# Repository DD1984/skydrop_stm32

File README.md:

this is port of SkyDrop vario to stm32vldiscovery board

origin code:
https://github.com/fhorinek/SkyDrop
website:
http://skybean.eu

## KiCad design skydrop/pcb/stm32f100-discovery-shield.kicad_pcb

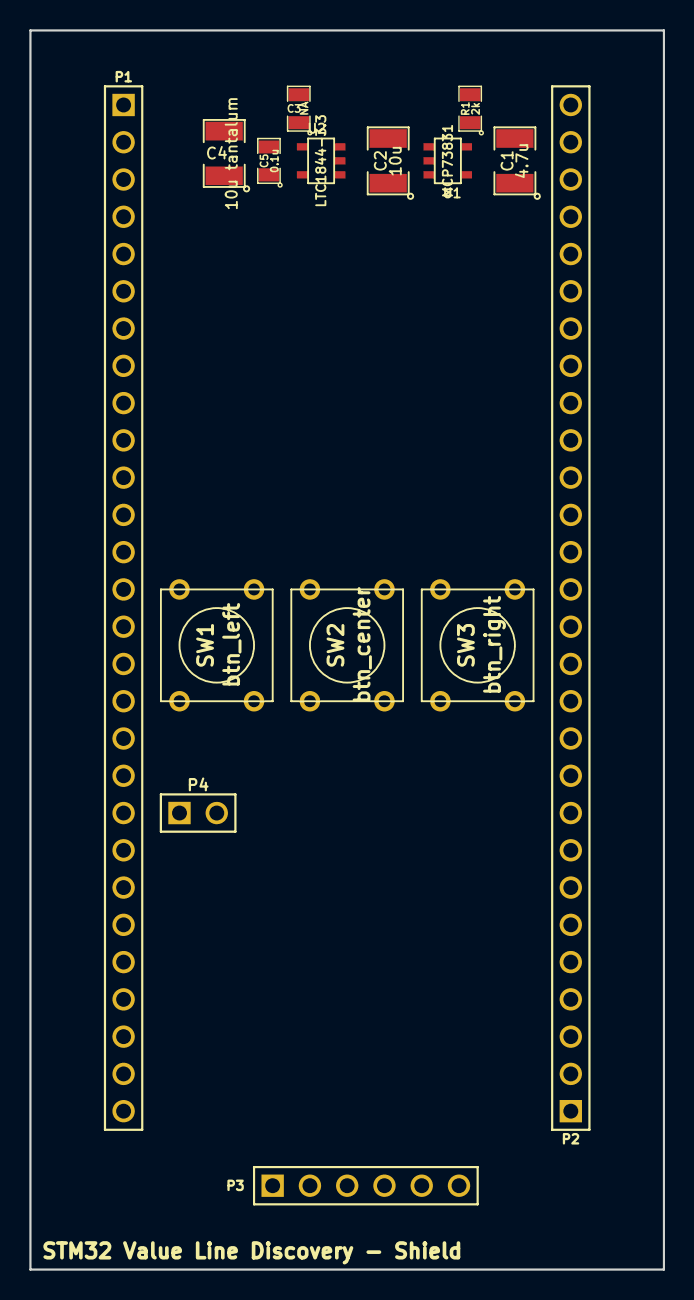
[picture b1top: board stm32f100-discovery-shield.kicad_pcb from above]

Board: 2 copper layers, 43.2 x 84.5 mm, 15 parts (0 on the bottom side), 9 nets, no tracks yet.

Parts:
C1: 4.7u; SM1210
C2: 10u; SM1210
C3: NA; SM0805
C4: 10u tantalum; SM1210
C5: 0.1u; SM0805
P1, P2: CONN28; PIN_ARRAY_28X1
P3: CONN6; PIN_ARRAY_6X1
P4: CONN_2; PIN_ARRAY_2X1
R1: 2k; SM0805
SW1: btn_left; SW_PUSH_SMALL
SW2: btn_center; SW_PUSH_SMALL
SW3: btn_right; SW_PUSH_SMALL
U1: MCP73831; SOT23-5
U2: LTC1844-3.3; SOT23-5

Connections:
+3.3V: C4.1, C5.1, P4.1, SW1.1, SW3.1, U2.5
+5V: C1.1, P2.26, U1.4
+BATT: C2.1, U1.3, U2.1
GND: C1.2, C2.2, C3.2, C4.2, C5.2, P1.1, P1.28, P2.1, P2.28, R1.2, U1.2, U2.2
unnamed: C3.1, U2.4
unnamed: R1.1, U1.5
btn_center: P1.15, SW2.2
btn_left: P2.9, SW1.2
btn_right: P2.10, SW3.2

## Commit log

2015-10-07 first stm32 build
2015-10-08 add hal files
2015-10-08 simple changes
2015-10-12 Makefile
2015-10-12 add other hal files
2015-10-12 first build with gui
2015-10-16 hal reorganosation
2015-10-16 GUI tasks form define to enum
2015-10-16 syscall for write to lcd
2015-10-16 init FILE *lcd_out
2015-10-16 some defines changes
2015-10-16 add display support for stm32 and add support TFT_ILI9163C - all veru ugly
2015-10-16 set_system: some code under define
2015-10-16 settings: some code under define
2015-10-16 add button support for stm32
2015-10-16 linkage lcd output function for C and C++
2015-10-16 change Makefile, remember -O1 instead -Os
2015-10-16 error in type cast in font in lcd:write
2015-10-16 button rebind adn fix uart output
2015-10-19 add hal files for timers
2015-10-19 remove STM32 define from fonts - restore PROGMEM
2015-10-19 ls scripts - temporarily set ram end to 0x20001FF8 - needed for stack aligment(8) - for printf_float work
2015-10-19 redefine button, because pin pa1 are used for sound pwm
2015-10-19 remove STM32 define
2015-10-19 add battery stub, remove define BATTERY_SUPPORT, change define BUZZER_SUPPORT to AUDIO_SUPPORT
2015-10-19 add timers init hal functions
2015-10-19 remove widget constant numbers and change it to enum
2015-10-19 audio driver for stm32
2015-10-19 change BUZZER_SUPPORT define to AUDIO_SUPPORT
2015-10-19 remove STM32 define for PROGMEM
2015-10-19 add some code under RTC_SUPPORT
2015-10-19 default config support
2015-10-19 PROGMEM, pgm_read_* realisation for stm32
2015-10-21 fully worked audio driver
2015-10-29 remove audio_step call from tick intrrupt
2015-10-29 hal i2c support and dedicated file for timer interrupt handlers
2015-10-29 add bmp180 support
2015-10-29 rename audio timer handler
2015-10-29 remove second i2c init functions
2015-10-29 bmp180 support fc_meas_timer handler kalman filter with variable parameter for debug use
2015-11-04 hal reorganization
2015-11-04 simple eeprom realisation, w/o power loss protection
2015-11-05 - add hal file for power control and rtc - add rtc support with hal modification (not good, but simple) - system reset realisation
2015-11-05 add StandBY mode
2015-11-06 add menu items GPS under define
2015-11-09 move ILI9163C support to separate files
2015-11-09 remove define DISPLAY_SUPPORT
2015-11-09 change #ifdef FC_TIMER to #ifndef STM32
2015-11-09 remove define RTC_SUPPORT
2015-11-09 remove define AUDIO_SUPPORT
2015-11-09 remove define UART_SUPPORT
2015-11-10 remove define WDT_SUPPORT, but wdt not implemented
2015-11-14 change timers MspInit function
2015-11-14 remove bmp180 support and add ms5611
2015-11-14 debug print - unbuffering output
2015-11-14 restore original kalman filter code, filter init w/o new
2015-11-14 makefile and debug message about heap and stack collision
2015-11-15 - temperature from ms5611 - data structures for acc and gyro and its widget under define
2015-11-15 additional for prevision commit
2015-11-15 add mass storage settings under define, and fix bug with widgets
2015-11-15 enable 5110 support
2015-11-15 poll buttons one time in mstick
2015-11-20 1. check PROM crc for ms5611 2. buzzer to tim1 for synphase signal to buzzer 3. lcd off in powerdown
2015-11-20 edit README.md1
2015-11-24 start pcb design
2015-12-30 bat adc
2016-01-02 bat support
2016-08-03 hal for stm32f103xe
2016-08-03 stm32f103 i2c work with hack
2016-08-03 [103] ld scripts - temporarily set ram end to 0x20001FF8 - needed for stack aligment(8) - for printf_float work
2016-08-03 ld script 103 - add eeprom section
2016-08-04 rotate display
2016-11-15 - change uart1->uart3 - change display and keys mapping - add H-bridge support
2016-11-17 battery remap, check usb power and charge status
2016-11-17 power_down - default task
2016-11-24 pcb in eagle
2016-12-04 change buttons, bat_en mapping, remove N pwm func
2016-12-04 pcb improovment, gitignore change
2016-12-07 start spi flash support
2016-12-08 add files to gitignore
2016-12-08 add eagle lck file to gitignore
2016-12-08 start usb support
2016-12-08 restore pcb
2016-12-08 change usb disconnect pin
2016-12-08 usb clock
2016-12-08 gitignore
2016-12-09 spi flash driver improovment
2016-12-09 usb flash support, note: only 512b from 4kb sector support
2016-12-10 add 4kb flash sector support
2016-12-11 add exFat support
2016-12-12 first build with logger support
2016-12-12 first build with gps support
2016-12-14 fix after merge
2016-12-14 fix after merge #2
2016-12-14 fix after merge #3
2016-12-14 first successeful build after merge
2016-12-14 half fix: time, debug, task_timer
2016-12-17 - fix reset status - temporary comment gps uart function - add button port cloock enable
2016-12-17 fix battery indicator
2016-12-17 usb MS fix
2016-12-17 - stop fc_meas_timer before ms5611 poweroff - decrease clock 72MHZ -> 48mHZ for smt32 internal flash write work - may be need to use FLASH_SR_EOP instead FLASH_SR_BSY - unmount fs
2016-12-18 eeprom impovement
2016-12-18 - place config_ro from .cfg_ro to eeprom section - reset flash configuration after stlink programming - for eeprom work after programming
2016-12-19 add stop fc_meas_timer before start, add start ms5611 measurement
2016-12-19 set baro valid timer to old 12s value - temporary
2016-12-21 fix: battry charge status
2016-12-21 audio: delete unused code
2017-01-05 - change buttons poll freq - first power on always in active task
2017-01-05 deep power mode for spi flash
2017-01-06 - SysTick priority more then usb irq priority - for delay work in usb irq - deinit usb
2017-01-06 fix debug log
2017-01-11 start gps uart support
2017-01-11 fix gps uart deinit
2017-01-11 fix battery callibration
2017-01-12 change %S->%s
2017-01-12 remove LOGGER_SUPPORT define from logger.cpp
2017-01-13 comment f_sync in logger - this is very slowly on spi flash and not needed at all with battry power
2017-01-18 fix vario & demo vario
2017-01-19 fix time setup on first power on
2017-01-20 reading from gps uart only if it initialized
2017-01-22 add DEBUG macro for C source
2017-01-22 fix two crashes in usb without host (only charger)
2017-01-23 improve pcb
2017-01-30 [pcb] new display
2017-03-10 improve pcb for new display
2017-03-10 display docs
2017-03-10 wdg support
2017-05-25 add spi extender
2017-05-25 improove spi extender
2017-05-29 [pcb] improove
2017-05-30 [pcb] improve
